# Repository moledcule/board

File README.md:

# Moledcule Board

This repository contains the design and firmware for the main controller board of the Moledcule System. The board is based on the Atmel 32u4 MCU and serves as the central processing unit for the Moledcule ecosystem.

## Table of Contents

- [Overview](#overview)
- [Features](#features)
- [Requirements](#requirements)
- [Installation](#installation)
- [Usage](#usage)
- [Contributing](#contributing)
- [License](#license)

## Overview

The Moledcule Board is the primary controller for the Moledcule System. It is built around the Atmel 32u4 microcontroller and includes various components and connectors to interface with other parts of the system. This board handles the main processing tasks, communication, and control of the Moledcule ecosystem.

## Features

- Based on Atmel 32u4 MCU
- Multiple GPIO pins for interfacing with sensors and actuators
- USB connectivity for power and programming
- Integrated voltage regulators
- Easy to integrate with other Moledcule components

## Requirements

- Moledcule Board PCB
- Micro-USB cable for power and programming
- Development environment set up (e.g., Arduino IDE)
- Required libraries and dependencies

## Installation

1. **Hardware Setup:**
   - Assemble the Moledcule Board with all necessary components.
   - Connect the board to your computer using a Micro-USB cable.

2. **Software Setup:**
   - Clone the repository:

     ```bash
     git clone https://github.com/moledcule/board.git
     cd board
     ```

   - Install the necessary libraries for the Atmel 32u4. For example, if using the Arduino IDE:

     ```bash
     arduino-cli lib install "Adafruit AVR Boards"
     ```

   - Open the provided firmware code in the Arduino IDE and upload it to the Moledcule Board.

## Usage

1. Connect the Moledcule Board to your computer or power source.
2. Use the provided firmware to interface with the board and perform tasks such as reading sensor data or controlling actuators.
3. Customize the firmware to fit your specific use case within the Moledcule ecosystem.

## Contributing

We welcome contributions to the Moledcule Board project. To contribute:

1. Fork the repository.
2. Create a new branch for your feature or bug fix.
3. Make your changes and commit them with descriptive messages.
4. Push your changes to your fork.
5. Create a pull request to the main repository.

## License

This project is licensed under the MIT License. See the [LICENSE](LICENSE) file for details.

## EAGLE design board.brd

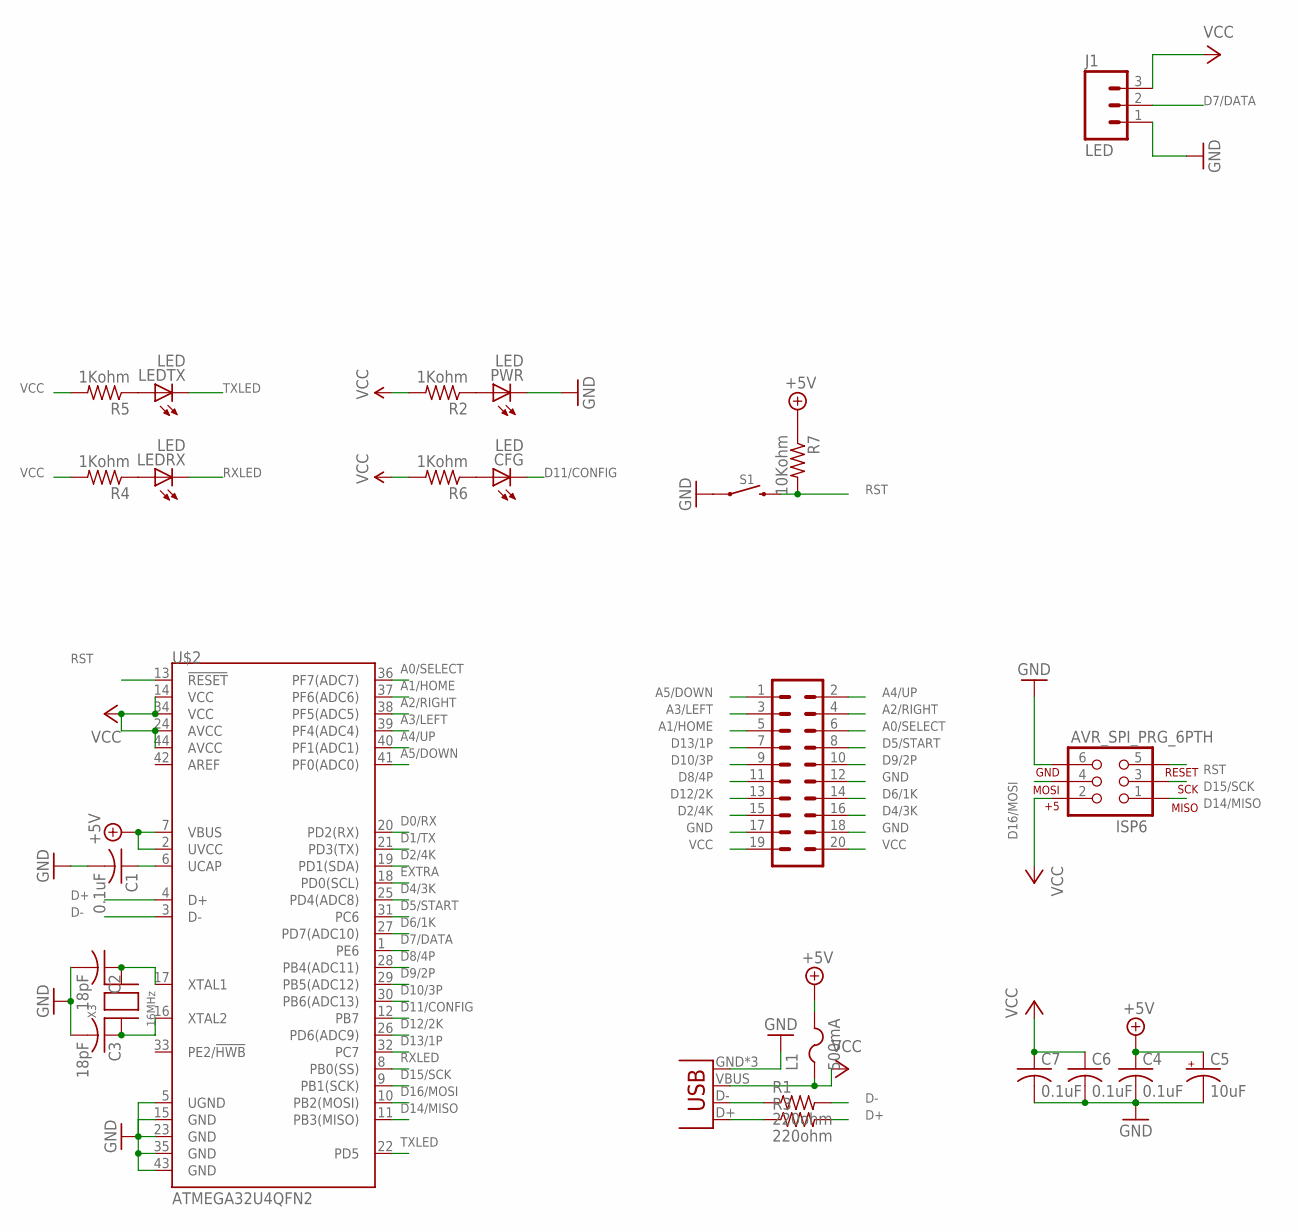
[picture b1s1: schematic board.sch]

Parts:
C1, C4, C6, C7: 0.1uF; C0603
C2, C3: 18pF; C0603
C5: 10uF; 0603-POLAR
CFG: LED; CHIPLED_0603
CN1: USB-MICROB
ISP6: AVR_SPI_PRG_6PTH; 2X3
J1: LED; JST-3-PTH-VERT
L1: 500mA; R1206
LEDRX: LED; CHIPLED_0603
LEDTX: LED; CHIPLED_0603
PWR: LED; CHIPLED_0603
R1, R3: 220ohm; R0603
R2, R4, R5, R6: 1Kohm; R0603
R7: 10Kohm; R0603
S1: MOMENTARY-SWITCH-SPST-SMD-4.6X2.8MM; TACTILE_SWITCH_SMD_4.6X2.8MM
U$1: M10X2; 2X10
U$2: ATMEGA32U4QFN2; SPARKFUN-DIGITALIC_QFN-44-NOPAD
X3: 16MHz; NX5032

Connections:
+5V: C4.1, C5.+, L1.2, R7.1, U$2.2 (UVCC), U$2.7 (VBUS)
A0/SELECT: U$1.6, U$2.36 (PF7(ADC7))
A1/HOME: U$1.5, U$2.37 (PF6(ADC6))
A2/RIGHT: U$1.4, U$2.38 (PF5(ADC5))
A3/LEFT: U$1.3, U$2.39 (PF4(ADC4))
A4/UP: U$1.2, U$2.40 (PF1(ADC1))
A5/DOWN: U$1.1, U$2.41 (PF0(ADC0))
D0/RX: U$2.20 (PD2(RX))
D1/TX: U$2.21 (PD3(TX))
D2/4K: U$1.15, U$2.19 (PD1(SDA))
D4/3K: U$1.16, U$2.25 (PD4(ADC8))
D5/START: U$1.8, U$2.31 (PC6)
D6/1K: U$1.14, U$2.27 (PD7(ADC10))
D7/DATA: J1.2, U$2.1 (PE6)
D8/4P: U$1.11, U$2.28 (PB4(ADC11))
D9/2P: U$1.10, U$2.29 (PB5(ADC12))
D10/3P: U$1.9, U$2.30 (PB6(ADC13))
D11/CONFIG: CFG.C, U$2.12 (PB7)
D12/2K: U$1.13, U$2.26 (PD6(ADC9))
D13/1P: U$1.7, U$2.32 (PC7)
D14/MISO: ISP6.1, U$2.11 (PB3(MISO))
D15/SCK: ISP6.3, U$2.9 (PB1(SCK))
D16/MOSI: ISP6.4, U$2.10 (PB2(MOSI))
D+: R3.2, U$2.4 (D+)
D-: R1.2, U$2.3 (D-)
EXTRA: U$2.18 (PD0(SCL))
GND: C1.2, C2.2, C3.2, C4.2, C5.-, C6.2, C7.2, CN1.GND, CN1.MT1 (GND), CN1.MT2 (GND), ISP6.6, J1.1, PWR.C, S1.1, S1.2 (1), U$1.12, U$1.17, U$1.18, U$2.5 (UGND), U$2.15 (GND), U$2.23 (GND), U$2.35 (GND), U$2.43 (GND)
unnamed: CFG.A, R6.1
unnamed: PWR.A, R2.1
unnamed: CN1.D+, R3.1
unnamed: CN1.D-, R1.1
unnamed: LEDRX.A, R4.1
unnamed: LEDTX.A, R5.1
unnamed: C2.1, U$2.17 (XTAL1), X3.P$2
unnamed: C3.1, U$2.16 (XTAL2), X3.P$1
RST: ISP6.5, R7.2, S1.3 (2), S1.4 (2), U$2.13 (!RESET)
RXLED: LEDRX.C, U$2.8 (PB0(SS))
TXLED: LEDTX.C, U$2.22 (PD5)
UCAP: C1.1, U$2.6 (UCAP)
VCC: C6.1, C7.1, CN1.VBUS, ISP6.2, J1.3, L1.1, R2.2, R4.2, R5.2, R6.2, U$1.19, U$1.20, U$2.14 (VCC), U$2.24 (AVCC), U$2.34 (VCC), U$2.44 (AVCC)

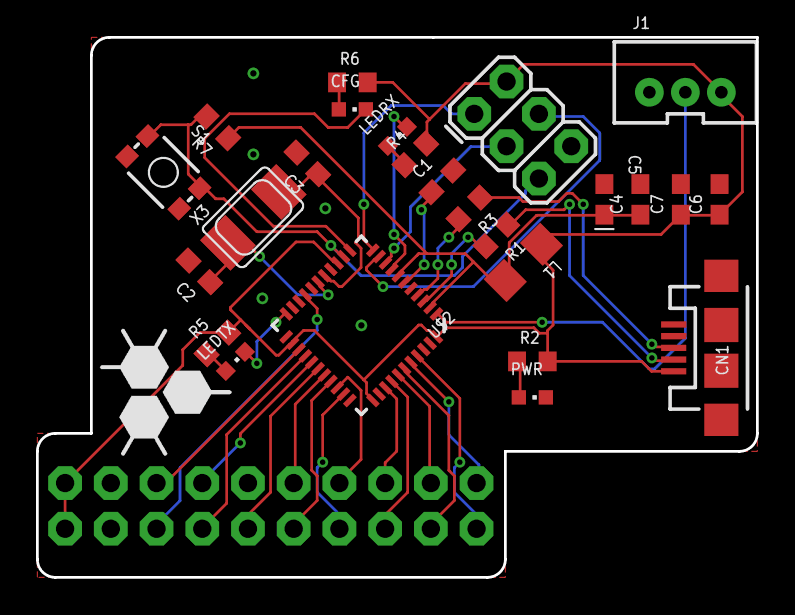
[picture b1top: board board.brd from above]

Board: 2 copper layers, 40.0 x 30.0 mm, 26 parts (1 on the bottom side), 37 nets.

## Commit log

2019-09-09 Mon 9 Sep 2019 10:56:58 EDT - Split Main Board from original 'Moledcule' Organization
2024-07-25 README.md

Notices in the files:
parts and their libraries:
SparkFun-Connectors: Licensing: CC v3.0 Share-Alike You are welcome to use this library for commercial purposes.
SparkFun-Retired: Licensing:Creative Commons ShareAlike 4.0 International - https://creativecommons.org/licenses/by-sa/4.0
